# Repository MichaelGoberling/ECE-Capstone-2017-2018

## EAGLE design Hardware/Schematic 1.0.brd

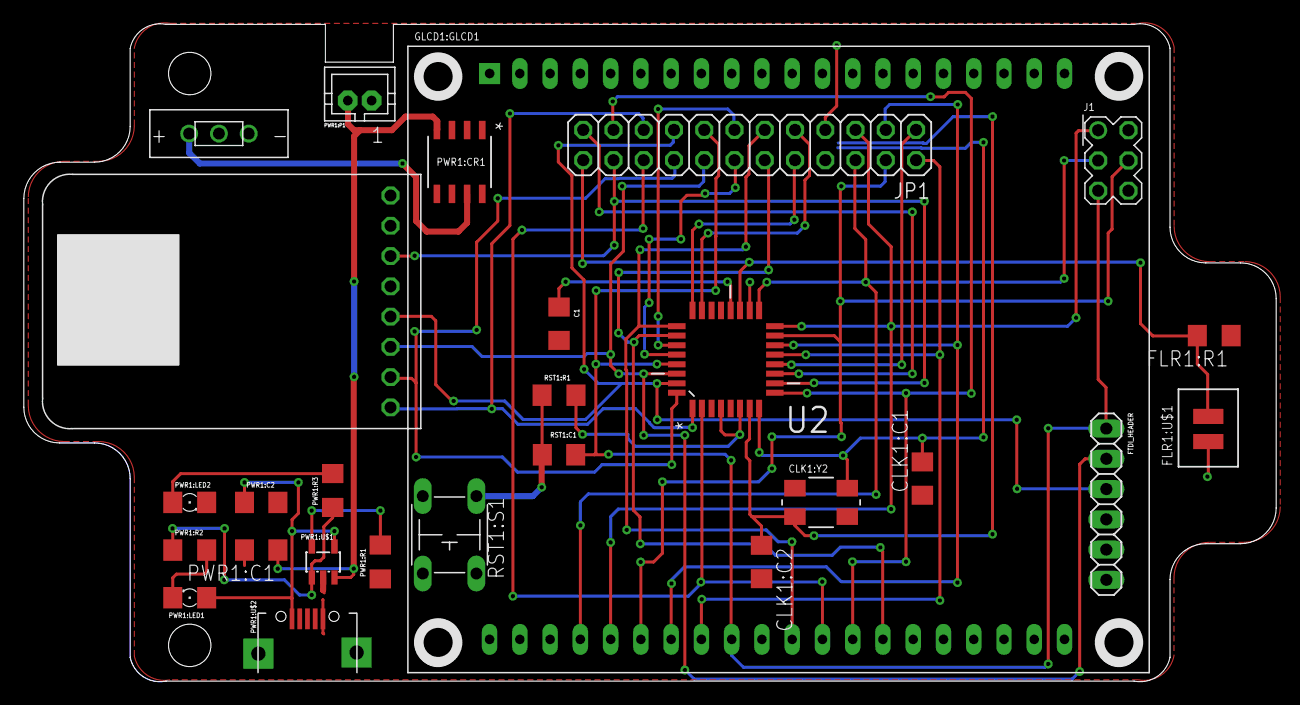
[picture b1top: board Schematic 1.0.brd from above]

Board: 2 copper layers, 105.1 x 55.2 mm, 58 parts (0 on the bottom side), 35 nets.

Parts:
BLE-UART:U$1: BLE-UART
BLE-UART:U$2: NC
C1: 0.1uF; C1206
CLK1:C1, CLK1:C2: 22pF; C1206
CLK1:Y2: ABMM2-8.000MHZ-E2-T; CRYSTAL_ABMM2
FLR1:R1: 10k; R1206
FLR1:U$1: FSL0095103ST
FTDI_HEADER: 1X06
GLCD1:GLCD1: GLCD_240X320
GLCD1:U$1, GLCD1:U$2, GLCD1:U$3, GLCD1:U$4, GLCD1:U$5, GLCD1:U$6, GLCD1:U$7, GLCD1:U$8, GLCD1:U$9, GLCD1:U$10, GLCD1:U$11, GLCD1:U$12, GLCD1:U$13, GLCD1:U$14, GLCD1:U$15, GLCD1:U$16, GLCD1:U$17, GLCD1:U$18, GLCD1:U$19, GLCD1:U$20, GLCD1:U$21, GLCD1:U$22, GLCD1:U$23, GLCD1:U$24, GLCD1:U$25, GLCD1:U$26, GLCD1:U$27, GLCD1:U$29: NC
J1: AVR-ISP-6PINAVR-ISP-6PIN-SMALL-SILK; AVR-ISP-6PIN-SMAILL-SILK
JP1: 2X12
PWR1:C1, PWR1:C2: 0.1uF; C1206
PWR1:CR1: LD1117D33CTR; SO-8
PWR1:LED1, PWR1:LED2: 1206
PWR1:P1: JST-PH2
PWR1:R1: 2k; R1206
PWR1:R2, PWR1:R3: 470; R1206
PWR1:U$1: MCP73831; SOT23-5L
PWR1:U$2: MICRO-USB
PWR1:U$3, PWR1:U$4: NC
PWR1:U$5: EG1218-PWR-SW
RST1:C1: 0.1uF; C1206
RST1:R1: 10k; R1206
RST1:S1: SW-SPST-TACT-4
U2: ATMEGA328P-AU; QFP80P900X900X120-32N

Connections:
1/PD3/BLE_MOD: BLE-UART:U$1.1, JP1.19, U2.1
2/PD4/LCD_X+: GLCD1:GLCD1.32, JP1.20, U2.2
7/PB6/XTAL1: CLK1:C2.1, CLK1:Y2.3, U2.7
8/PB7/XTAL2: CLK1:C1.2, CLK1:Y2.1, U2.8
9/PD5/LCD_Y-: GLCD1:GLCD1.33, JP1.21, U2.9
10/PD6/BLE_RTS: BLE-UART:U$1.6, JP1.22, U2.10
13/PB1/LCD_C/!D: GLCD1:GLCD1.28, JP1.2, U2.13
14/PB2/!LCD_CS: GLCD1:GLCD1.27, JP1.3, U2.14
15/PB3/MOSI: GLCD1:GLCD1.26, J1.MOSI, JP1.4, U2.15
16/PB4/MISO: GLCD1:GLCD1.25, J1.MISO, JP1.5, U2.16
17/PB5/SCK: GLCD1:GLCD1.24, J1.SCK, JP1.6, U2.17
19/ADC6: FLR1:R1.2, FLR1:U$1.-, JP1.24, U2.19
25/PC2/LCD_Y+: GLCD1:GLCD1.31, JP1.11, U2.25
26/PC3/LCD_X-: GLCD1:GLCD1.34, JP1.12, U2.26
29/PC6/!RESET: FTDI_HEADER.1, GLCD1:GLCD1.29, J1.RESET, JP1.15, RST1:C1.2, U2.29
32/PD2/BLE_CTS: BLE-UART:U$1.2, JP1.18, U2.32
ATRXD_BLTXD: BLE-UART:U$1.3, FTDI_HEADER.2, JP1.16, U2.30
ATTXD_BLRXD: BLE-UART:U$1.4, FTDI_HEADER.3, JP1.17, U2.31
GND: BLE-UART:U$1.7, C1.2, CLK1:C1.1, CLK1:C2.2, CLK1:Y2.2, CLK1:Y2.4, FLR1:R1.1, FTDI_HEADER.5, FTDI_HEADER.6, GLCD1:GLCD1.1, GLCD1:GLCD1.21, J1.GND, JP1.8, PWR1:C1.2, PWR1:C2.2, PWR1:CR1.1, PWR1:LED2.C, PWR1:P1.1, PWR1:R1.1, PWR1:U$1.2, PWR1:U$2.5, PWR1:U$2.GND1, PWR1:U$2.GND2, PWR1:U$5.3, RST1:S1.1B, U2.3, U2.5, U2.21
unnamed: C1.1, U2.20
PB0: JP1.1, U2.12
PC0: JP1.9, U2.23
PC1: JP1.10, U2.24
PC4: JP1.13, U2.27
PC5: JP1.14, U2.28
PD7: JP1.23, U2.11
PWR1:N$1: PWR1:C2.1, PWR1:LED1.A, PWR1:U$1.4, PWR1:U$2.1
PWR1:N$2: PWR1:LED1.C, PWR1:R2.2
PWR1:N$3: PWR1:R2.1, PWR1:R3.1, PWR1:U$1.1
PWR1:N$4: PWR1:LED2.A, PWR1:R3.2
PWR1:N$5: PWR1:R1.2, PWR1:U$1.5
PWR1:N$6: PWR1:CR1.7, PWR1:U$5.1
PWR1:NS10: PWR1:C1.1, PWR1:CR1.4, PWR1:P1.2, PWR1:U$1.3
RST1:N$1: RST1:C1.1, RST1:R1.1, RST1:S1.2A
VCC: BLE-UART:U$1.5, FLR1:U$1.+, FTDI_HEADER.4, GLCD1:GLCD1.22, JP1.7, PWR1:U$5.2, RST1:R1.2, U2.4, U2.6, U2.18

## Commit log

2018-03-01 Capstone 0.1
2018-03-02 Test
2018-03-02 Test 2
2018-03-02 Test 0.3
2018-03-02 Restart
2018-03-02 TestBOI
2018-03-02 stuff
2018-03-02 Version 0.1
2018-03-02 Version 0.2
2018-03-02 Version 0.3
2018-03-05 Version 0.4
2018-03-08 Version 0.5
2018-03-12 Version 0.6
2018-03-13 Version 0.7
2018-03-29 Version 0.8
2018-04-09 Added Newest Hardware
2018-04-12 Version 0.9
2018-04-14 Version 1.0
2018-04-17 Version 1.1
2018-04-19 Version 1.2
2018-04-19 Calibration Push
2018-04-22 Version 1.3
